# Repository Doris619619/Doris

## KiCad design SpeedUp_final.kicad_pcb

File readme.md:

以下步骤编译
```bash
# 解压压缩包
unzip pb2025_infantry_ws.zip
# 进入工作空间
cd pb2025_infantry_ws/
# 完成依赖安装
sudo rosdep init
rosdep update
rosdep install -r --from-paths src --ignore-src --rosdistro $ROS_DISTRO -y
# 开始编译
colcon build --symlink-install --cmake-args -DCMAKE_BUILD_TYPE=Release --parallel-workers 10
# 如果编译卡住，说明电脑性能不行，把10改小
```

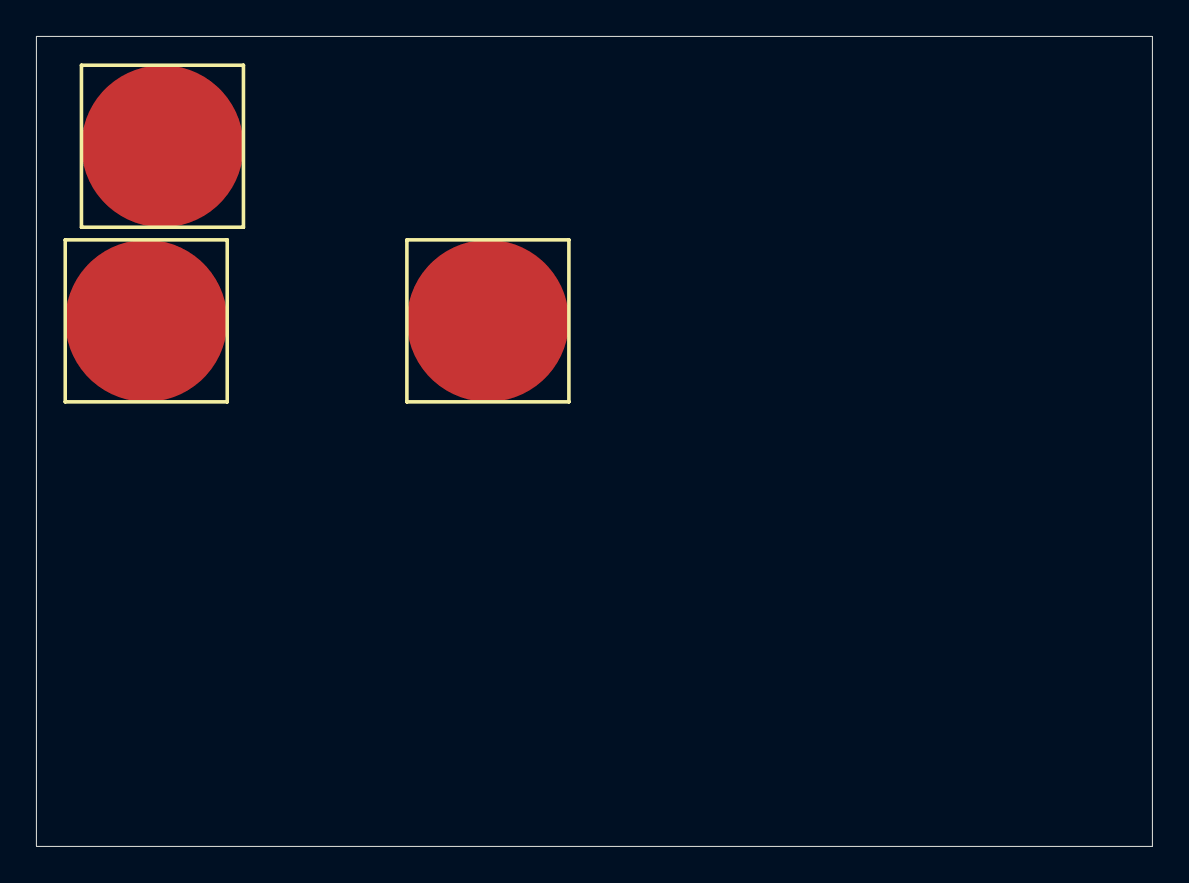
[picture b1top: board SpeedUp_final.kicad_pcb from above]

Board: 2 copper layers, 62.0 x 45.0 mm, 42 parts (0 on the bottom side), 21 nets, no tracks yet.

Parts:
0: TK-8MM_1
1: TK-8MM_2
2: TK-8MM_3
3: R1206-JP_4
4: SMD-EC6.3X6.3X10_5
5: SOT89-3_6
6: 0805_C_7
7: 1206_C_8
8: PWR_PAD_9
9: 0603_R_10
10: CDRH6D38-3D_11
11: LED_DRIVER_1PIN_12
12: DO-214AC_13
13: 0603_C_14
14: SOT-89-MT5_N_15
15: 0603_c_16
16: ssop28_17
17: SMD-EC6.3X6.3X10_18
18: LED_DRIVER_1PIN_19
19: 0603_C_20
20: SMA-SS_21
21: R1206-JP_22
22: 0603_R_23
23: 0805_C_24
24: 0603_R_25
25: R1206-JP_26
26: 0603_R_27
27: 1206_C_28
28: 0805_C_29
29: CDRH6D38-3D_30
30: LED_DRIVER_1PIN_31
31: 0603_R_32
32: SOT-89-MT5_N_33
33: 0603_R_34
34: R1206-JP_35
35: SMA-SS_36
36: 0603_C_37
37: 0805_C_38
38: R1206-JP_39
39: 0805_C_40
40: LED_DRIVER_1PIN_41
41: 0603_R_42

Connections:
GND: 4.2, 5.2, 6.2, 7.2, 8.2, 12.1, 13.2, 14.2, 15.1, 16.28, 17.2, 19.1, 23.1, 26.1, 27.2, 32.2, 36.1, 37.1, 41.1
NetC5_2: 15.2, 16.3
NetD1_1: 29.2, 32.1, 35.1
NetD2_1: 10.2, 14.1, 20.1
NetR3_2: 3.1, 14.4, 25.2, 34.2
NetR12_1: 31.1, 32.3
NetR14_1: 14.3, 24.1
NetR15_2: 2.1, 9.2
NetR16_2: 0.1, 33.2
NetR19_2: 1.1, 22.2
PWM1: 16.17, 26.2, 31.2
PWM2: 16.16, 24.2, 41.2
TK3: 9.1, 16.15
TK4: 16.23, 33.1
TK5: 16.22, 22.1
VCC_5V: 5.1, 6.1, 13.1, 16.1, 36.2
VIN: 4.1, 5.3, 7.1, 8.1, 12.2, 14.5, 17.1, 19.2, 20.2, 21.1, 25.1, 27.1, 32.5, 34.1, 35.2, 38.1
W+: 21.2, 28.1, 32.4, 38.2, 40.1
W-: 18.1, 23.2, 28.2, 29.1
Y+: 3.2, 30.1, 39.1
Y-: 10.1, 11.1, 37.2, 39.2

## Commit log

2025-09-23 Create 增加footprint编号的版本
2025-12-04 Create MyAndGate VHDL implementation
    This file implements an 8-input AND gate in VHDL.
2025-12-04 Create 1111111111111
2025-12-04 Create PROJECT2
2025-12-04 Create project3
2025-12-04 Update project3
2026-02-15 Revise compat_matrix_marked.csv for updates
    Updated compatibility matrix with new fields and parameters.
2026-03-28 Create 1
